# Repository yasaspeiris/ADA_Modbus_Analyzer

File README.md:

# ADA_Modbus_Analyzer

This is a portable MODBUS-RTU Master made using a STM32F407 MCU and completely programmed using Ada. You can incorporate the mbus package (found in adambus/src/) in your own projects to communicate with Modbus enabled slave devices.

## Dependencies
You will need,
GNAT Programming Studio : https://www.adacore.com/download (Download both files)

Ada Drivers Library : https://github.com/AdaCore/Ada_Drivers_Library

## Links
Full Instructions : https://www.hackster.io/yasaspeiris/ada-modbus-analyzer-c84242

First Test : https://www.youtube.com/watch?v=bEcFYIxN1XE

Final Demo : https://www.youtube.com/watch?v=MtwckgqX_BE

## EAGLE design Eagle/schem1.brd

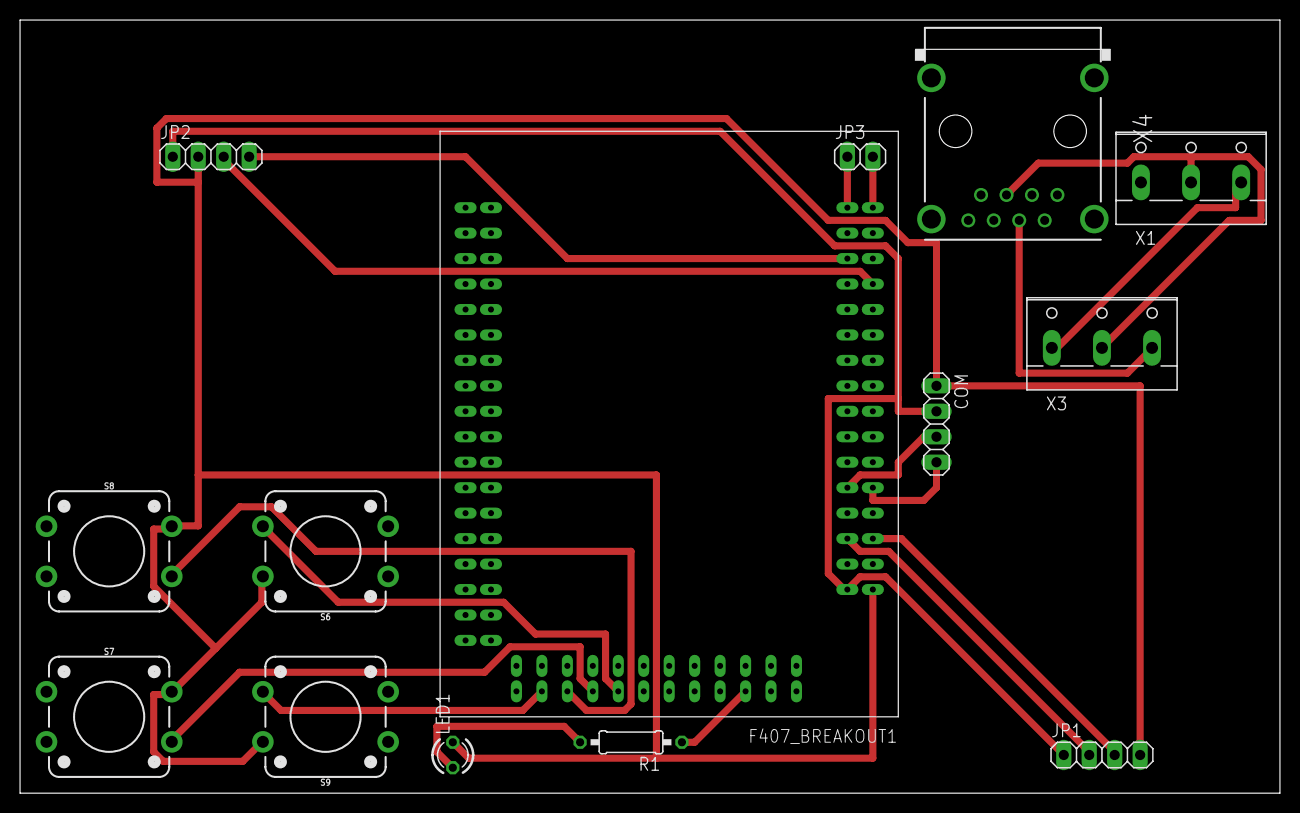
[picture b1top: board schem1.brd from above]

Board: 2 copper layers, 125.7 x 77.1 mm, 14 parts (0 on the bottom side), 19 nets.

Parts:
COM: 1X04
F407_BREAKOUT1: STM32F407_BREAKOUT
JP1, JP2: 1X04
JP3: 1X02
LED1: LED3MM
R1: 0207/10
S6, S7, S8, S9: MOMENTARY-SWITCH-SPST-PTH-12MM; TACTILE_SWITCH_PTH_12MM
X1, X3: W237-103
X4: RJ45-6L2-B; RJ45-SHIELD2

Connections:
A+: X3.3, X4.4
B-: X1.2, X3.2, X4.5
EARTH: X1.3, X3.1
GND: COM.1, F407_BREAKOUT1.GND@1, JP1.4, JP2.2, LED1.K, S6.3, S7.3, S8.3, S9.3
LED: F407_BREAKOUT1.PD14, R1.1
unnamed: LED1.A, R1.2
unnamed: F407_BREAKOUT1.GND@3, JP3.2
RX: F407_BREAKOUT1.PA10, JP1.3
SCL: F407_BREAKOUT1.PB6, JP2.3
SDA: F407_BREAKOUT1.PB7, JP2.4
SW1: F407_BREAKOUT1.PB12, S6.1
SW2: F407_BREAKOUT1.PB11, S7.1
SW3: F407_BREAKOUT1.PE15, S8.1
SW4: F407_BREAKOUT1.PE13, S9.1
SWCLK: COM.4, F407_BREAKOUT1.PA14
SWDIO: COM.3, F407_BREAKOUT1.PA13
TX: F407_BREAKOUT1.PA9, JP1.2
VBAT: F407_BREAKOUT1.VCC@5, JP3.1
VCC: COM.2, F407_BREAKOUT1.VCC@1, JP1.1, JP2.1

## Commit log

2019-02-14 Initial source commit
2019-02-14 Changed button layout and added the ability to set modbus slave address
2019-02-14 Fixed some Issues with the PCB
2019-02-15 3D Printed Enclosure
2019-02-15 Fixed a display issue after exiting register value screen
2019-02-16 Clear Response buffer after exit
2019-02-16 Added some small UI Improvements

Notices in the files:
parts and their libraries:
SparkFun-Switches: Licensing: Creative Commons ShareAlike 4.0 International - https://creativecommons.org/licenses/by-sa/4.0
